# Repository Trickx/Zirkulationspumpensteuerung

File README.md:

# Warmwasser-Sparpumpe
## für Heizkessel mit Zirkulationskreislauf

Auf Basis des [Heise Artikels zur Zirkulationspumpensteuerung](https://www.heise.de/select/make/2022/4/2216608454200440892) wurde diese Variante entworfen.
Sie enthält folgende Änderungen

* Software
  * Tasmota!
  * Pumpenlogik ist als Tasmota-Skript implementiert.

* Hardware
  * Verwendung einer NodeMCU anstelle eines reinen ESP8266-Modul.
  * Schraubklemmen für sämtliche Anschlüsse
  * 5V Stromversorgung anstelle eines eigenen Netzteils

||
|

## Scripting ist nicht vorkompilierten Tasmota-Binaries enthalten.
Das Default-Tasmota Projekt muss unter Zuhilfenahme einiger zusätzlicher Defines gebaut werden.
* [Anleitung](https://tasmota.github.io/docs/Scripting-Language/)

* Beachten Sie die einschlägigen VDE-Vorschriften.
* Keine Gewährleistung für irgendwas.

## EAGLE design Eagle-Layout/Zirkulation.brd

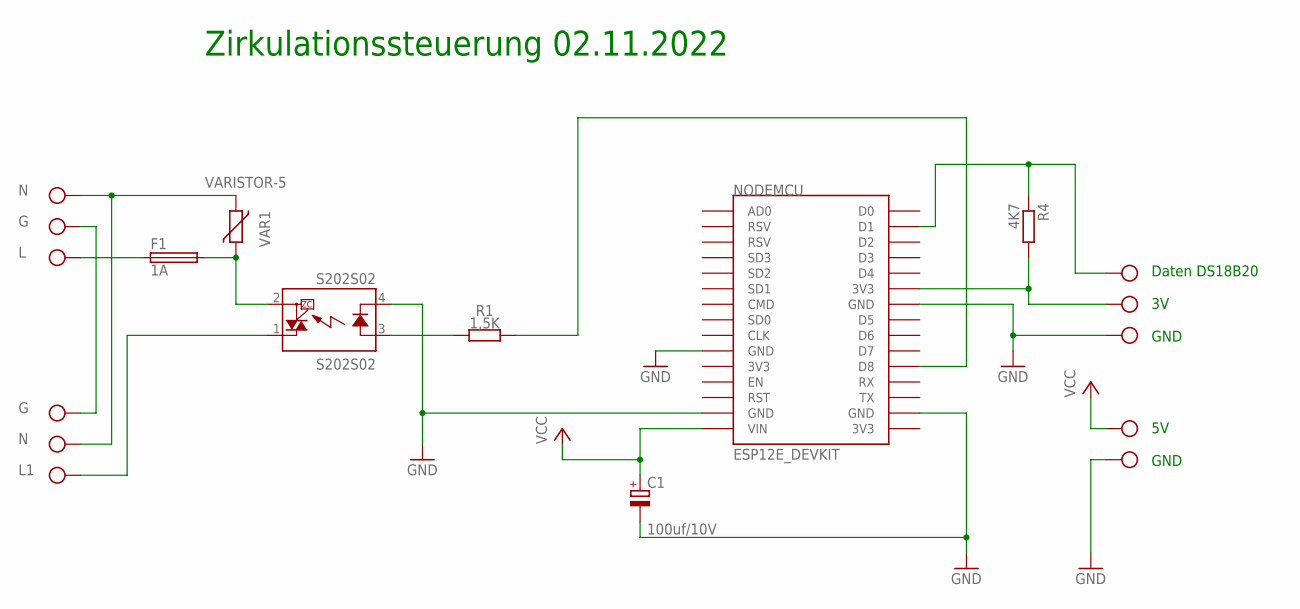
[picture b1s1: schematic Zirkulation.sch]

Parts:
C1: 100uf/10V; E2,5-7
F1: 1A; SH22,5
IN: MKDSN1,5/3-5,08
NODEMCU: ESP12E_DEVKIT
OUT: MKDSN1,5/3-5,08
PWR: MKDSN1,5/2-5,08
R1: 1,5K; 0204/5
R4: 4K7; 0204/5
S202S02: S202S02
SENSOR: MKDSN1,5/3-5,08
VAR1: VARISTOR-5; R-5

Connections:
G: IN.3, OUT.3
GND: C1.-, NODEMCU.GND@0 (GND), NODEMCU.GND@1 (GND), NODEMCU.GND@2 (GND), NODEMCU.GND@3 (GND), PWR.2, S202S02.4 (K), SENSOR.3
L: F1.1, IN.1
L1: OUT.1, S202S02.1 (DS1)
LF: F1.2, S202S02.2 (DS2), VAR1.1
N: IN.2, OUT.2, VAR1.2
unnamed: R1.2, S202S02.3 (A)
unnamed: NODEMCU.D8, R1.1
unnamed: NODEMCU.3V3@1 (3V3), R4.2, SENSOR.2
unnamed: NODEMCU.D1, R4.1, SENSOR.1
VCC: C1.+, NODEMCU.VIN, PWR.1

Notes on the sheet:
Zirkulationssteuerung 02.11.2022
Daten DS18B20 3V GND
5V GND

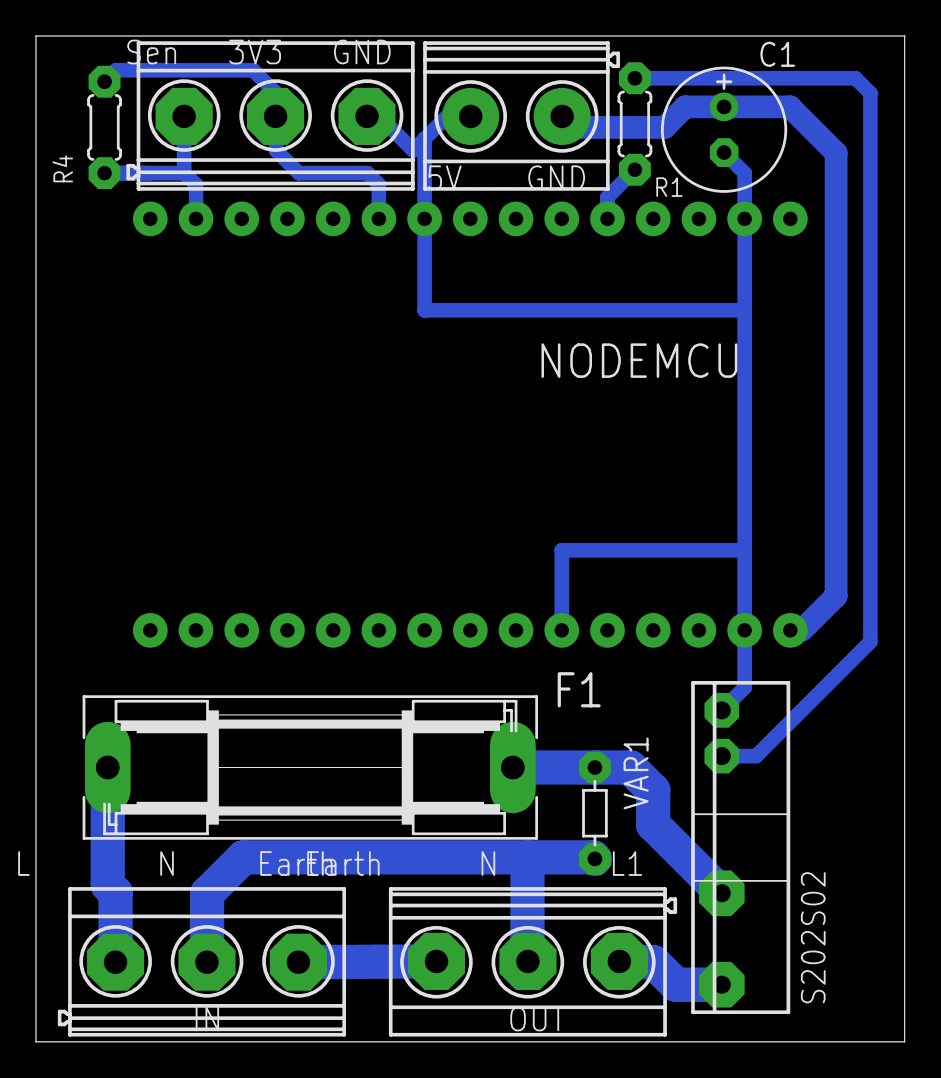
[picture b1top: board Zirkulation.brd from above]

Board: 2 copper layers, 48.3 x 55.9 mm, 11 parts (0 on the bottom side), 11 nets.

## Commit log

2022-11-02 Personal custom variant of Heise Zirkulationspumpe
2022-11-02 Added image of Tasmota Script
2022-11-02 Update README.md
    Initial documentation of my personal variant.
2022-11-02 Added screenshot of user_config_override
2022-11-02 Update README.md
    How to build.
2022-11-02 Updated screenshot of user_config_override
